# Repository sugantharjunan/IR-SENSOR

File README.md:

# IR Sensor Module – KiCad PCB Design

A compact and efficient **IR Sensor Module** designed using **KiCad EDA** for schematic design and PCB layout. This project uses an **IR LED transmitter**, **photodiode receiver**, and **LM393 comparator** to detect nearby objects through infrared reflection.

The module is suitable for robotics, obstacle detection, automation systems, and embedded electronics applications.

---

# Project Overview

This project demonstrates:

* IR object detection circuit
* PCB layout design in KiCad
* Compact sensor module design
* Comparator-based signal processing
* Adjustable detection sensitivity
* 3D PCB visualization

---

# Features

* Infrared object detection
* Adjustable sensing range
* Compact PCB design
* LM393 comparator output
* LED indication for detection status
* 3-pin output connector
* Designed using KiCad

---

# Software Used

* KiCad

Official Website: [KiCad Official Website](https://www.kicad.org?utm_source=chatgpt.com)

---

# Hardware Components

| Component     | Description                  |
| ------------- | ---------------------------- |
| LM393         | Voltage Comparator IC        |
| IR LED        | Infrared transmitter         |
| Photodiode    | IR receiver                  |
| Potentiometer | Sensitivity adjustment       |
| LEDs          | Status indication            |
| Resistors     | Current limiting and biasing |
| Capacitors    | Noise filtering              |
| 3-Pin Header  | Output connection            |

---

# Project Structure

```bash id="g5u2yi"
IR-SENSOR/
│
├── Schematic/
│   └── ir_sensor.kicad_sch
│
├── PCB/
│   └── ir_sensor.kicad_pcb
│
├── Gerber/
│   └── Manufacturing_Files
│
├── Images/
│   ├── IR_3D1.png
│   ├── IR_3D2.png
│   ├── IR_PCB.png
│   └── IR_SCHEMATIC.png
│
└── README.md
```

---

# Circuit Description

The IR sensor module works using infrared reflection.

## Working Principle

1. The IR LED emits infrared light continuously.
2. When an object comes near the sensor:

   * Infrared light reflects back.
3. The photodiode detects the reflected IR signal.
4. The LM393 comparator processes the signal.
5. Output pin changes state when detection occurs.
6. Indicator LED turns ON during object detection.

---

# PCB Design

The PCB was designed with:

* Compact component placement
* Proper grounding
* Short signal routing
* Easy connector access
* Single-layer routing structure
* Optimized IR sensor positioning

---
# Pin Configuration

| Pin | Description    |
| --- | -------------- |
| VCC | +5V Supply     |
| GND | Ground         |
| OUT | Digital Output |

---

# Electrical Specifications

| Parameter         | Value                |
| ----------------- | -------------------- |
| Operating Voltage | 5V DC                |
| Comparator IC     | LM393                |
| Sensor Type       | IR Reflective Sensor |
| Output Type       | Digital              |
| PCB Tool          | KiCad                |

---

# Applications

* Obstacle Avoiding Robots
* Line Following Robots
* Proximity Detection
* Industrial Automation
* Smart Vehicles
* Embedded Systems Projects
* IoT Applications

---

# Sensitivity Adjustment

The onboard potentiometer allows adjustment of detection sensitivity:

* Rotate clockwise → Increase sensitivity
* Rotate counterclockwise → Reduce sensitivity

---

# Future Improvements

* Add analog output support
* Add distance calibration
* Add onboard microcontroller
* Improve ambient light filtering
* Add SMT compact version

---

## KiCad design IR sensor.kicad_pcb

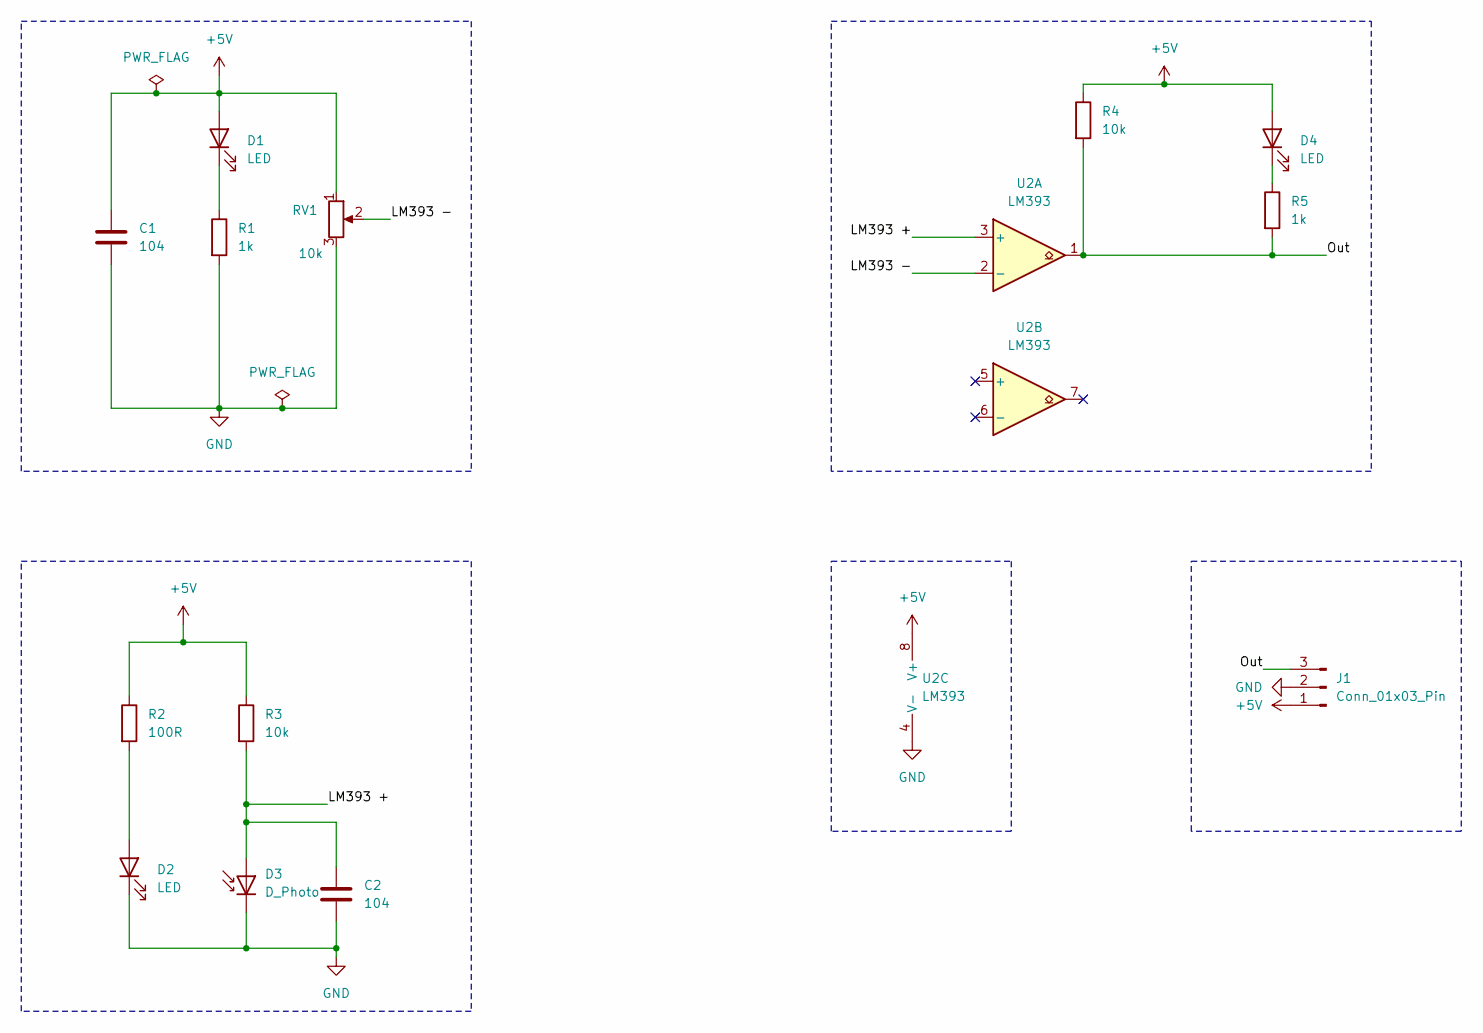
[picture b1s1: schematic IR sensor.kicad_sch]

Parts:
C1, C2: 104; C_0805_2012Metric
D1: LED; LED_D5.0mm_Clear
D2, D4: LED; LED_0603_1608Metric
D3: D_Photo; LED_D5.0mm_Horizontal_O1.27mm_Z3.0mm_IRBlack
J1: Conn_01x03_Pin; PinHeader_1x03_P2.54mm_Vertical
R1, R5: 1k; R_0603_1608Metric
R2: 100R; R_0805_2012Metric
R3, R4: 10k; R_0603_1608Metric
RV1: 10k; Potentiometer_Bourns_3266Y_Vertical
U2: LM393; SOIC-8_3.9x4.9mm_P1.27mm

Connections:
+5V: C1.1, D1.2 (A), D4.2 (A), J1.1, R2.1, R3.1, R4.1, RV1.1, U2.8 (V+)
/LM393 +: C2.1, D3.2 (A), R3.2, U2.3 (+)
/LM393 -: RV1.2, U2.2 (-)
/Out: J1.3, R4.2, R5.2, U2.1
GND: C1.2, C2.2, D2.1 (K), D3.1 (K), J1.2, R1.2, RV1.3, U2.4 (V-)
unnamed: D1.1 (K), R1.1
unnamed: D2.2 (A), R2.2
unnamed: D4.1 (K), R5.1

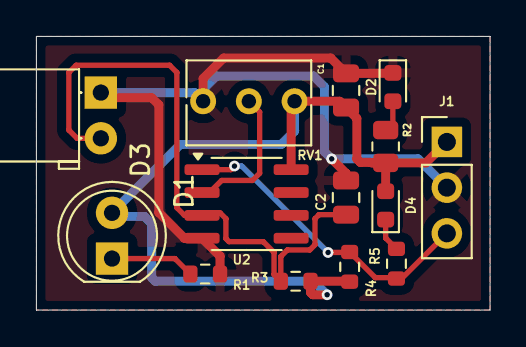
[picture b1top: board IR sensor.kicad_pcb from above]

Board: 2 copper layers, 25.2 x 15.2 mm, 14 parts (0 on the bottom side), 8 nets.
